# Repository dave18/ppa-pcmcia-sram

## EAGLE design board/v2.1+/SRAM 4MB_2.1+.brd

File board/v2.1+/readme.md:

This version is a small change to the 2.1 board.  Changes are:

* Allows use of 8mb version of SRAM - Note, this doesn't increases the memory from 4mb as the additional address pin is grounded. It is just for compatibility.
* Board parameters brought in line with PCBWay prototyping parameters to enable cheaper production
* PCMCIA connector moved 0.5mm closer to edge of board to fit with version I found at AliExpress.  https://www.aliexpress.com/item/4000671140408.html?spm=a2g0o.order_list.order_list_main.9.21ef1802yaBDrj

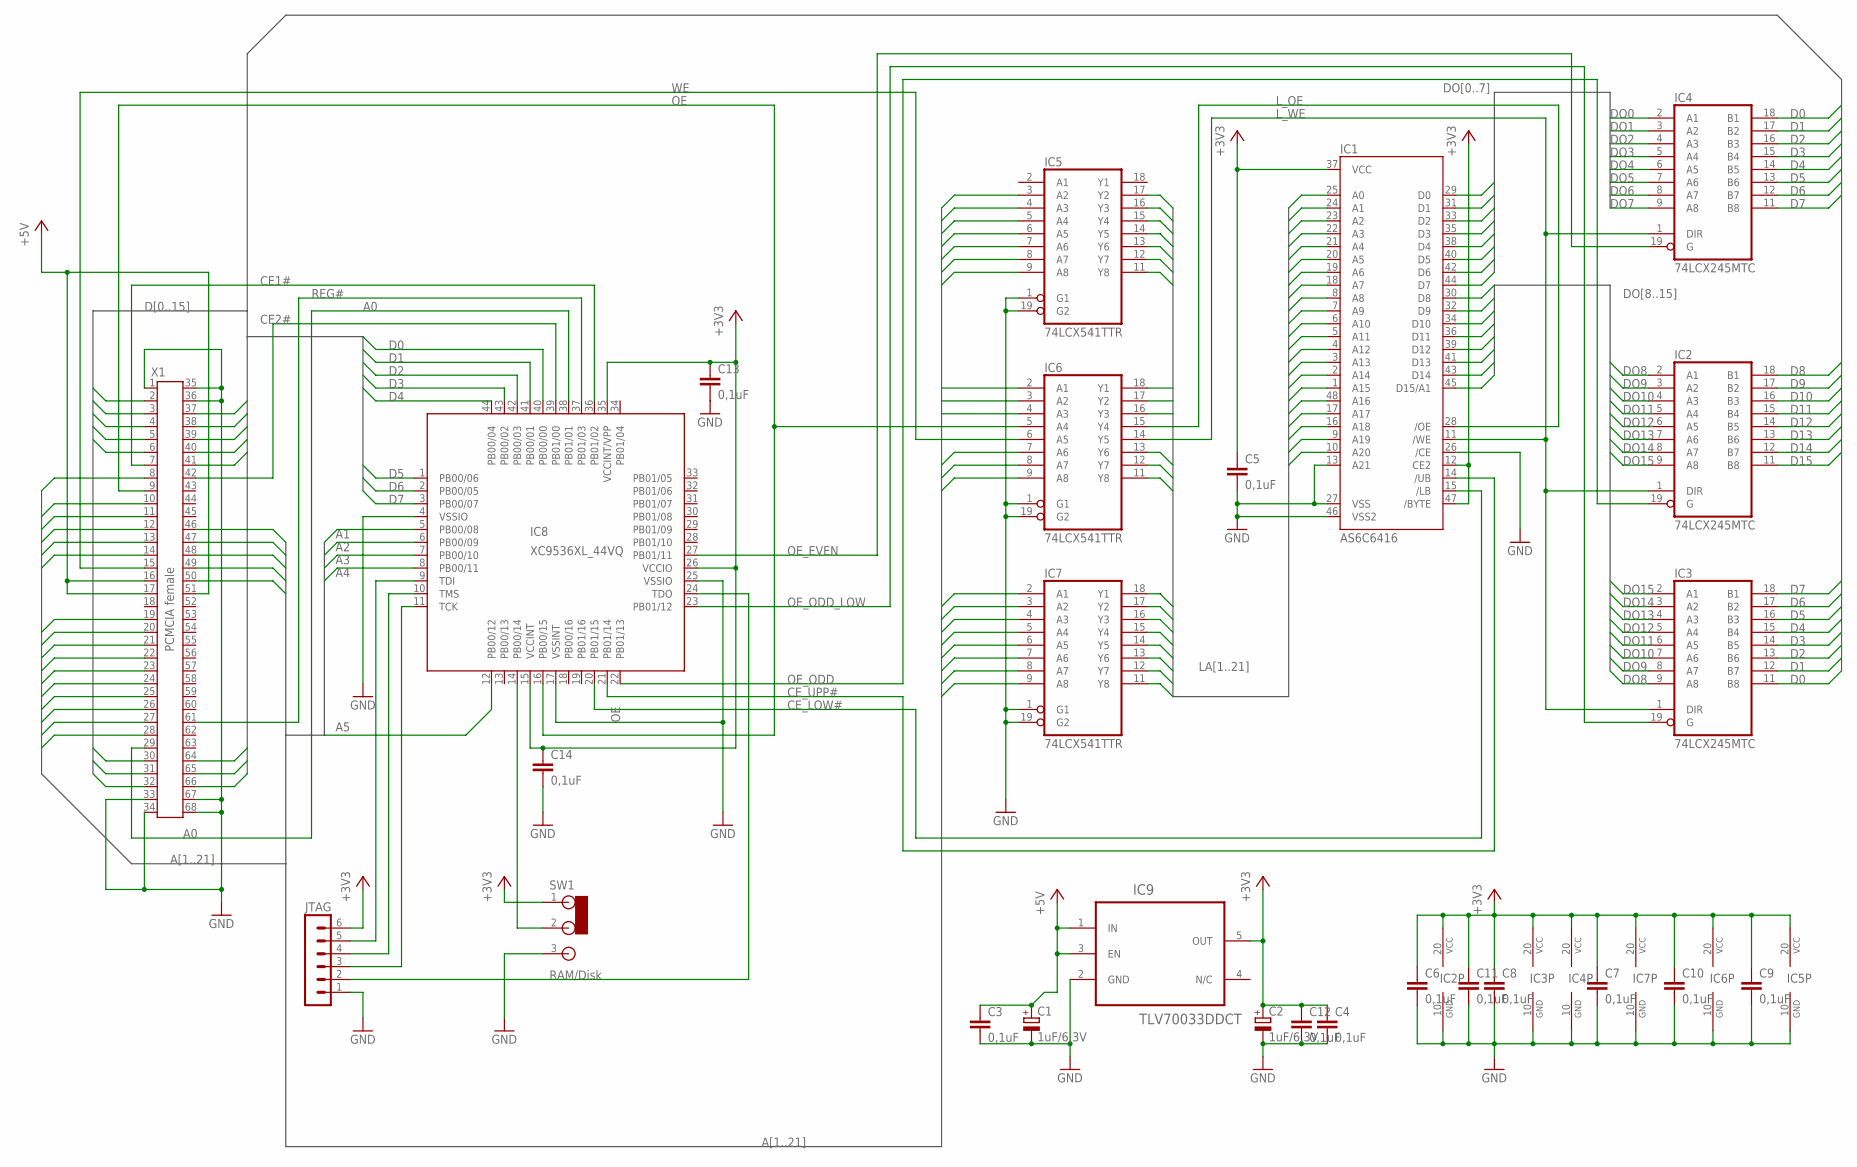
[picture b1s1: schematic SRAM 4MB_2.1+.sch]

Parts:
C1, C2: 1uF/6,3V; A/3216-18R
C3, C4: 0,1uF; C0603
C5, C6, C7, C8, C9, C10, C11, C12, C13, C14: 0,1uF; C0402K
IC1: AS6C6416; TSOP48
IC2, IC3, IC4: 74LCX245MTC; TSSOP20
IC5, IC6, IC7: 74LCX541TTR; TSSOP20
IC8: XC9536XL_44VQ; SQFP-S-10X10-44
IC9: TLV70033DDCT; SOT95P280X110-5N
JTAG: MA06-1
SW1: RAM/Disk; SWITCH2
X1: PCMCIA female; 9M681X04

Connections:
+3V3: C2.+, C4.1, C5.1, C6.1, C7.1, C8.1, C9.1, C10.1, C11.1, C12.1, C13.1, C14.1, IC1.12 (CE2), IC1.37 (VCC), IC1.47 (/BYTE), IC2.20 (VCC), IC3.20 (VCC), IC4.20 (VCC), IC5.20 (VCC), IC6.20 (VCC), IC7.20 (VCC), IC8.15 (VCCINT), IC8.26 (VCCIO), IC8.35 (VCCINT/VPP), IC9.5 (OUT), JTAG.6, SW1.1
+5V: C1.+, C3.1, IC9.1 (IN), IC9.3 (EN), X1.16, X1.17, X1.51
A0: IC8.38 (PB01/01), X1.29
A1: IC5.3 (A2), IC8.5 (PB00/08), X1.28
A2: IC5.4 (A3), IC8.6 (PB00/09), X1.27
A3: IC5.5 (A4), IC8.7 (PB00/10), X1.26
A4: IC5.6 (A5), IC8.8 (PB00/11), X1.25
A5: IC5.7 (A6), IC8.12 (PB00/12), X1.24
A6: IC5.8 (A7), X1.23
A7: IC5.9 (A8), X1.22
A8: IC7.6 (A5), X1.12
A9: IC7.7 (A6), X1.11
A10: IC7.9 (A8), X1.8
A11: IC7.8 (A7), X1.10
A12: IC6.2 (A1), X1.21
A13: IC7.4 (A3), X1.13
A14: IC7.2 (A1), X1.14
A15: IC6.3 (A2), X1.20
A16: IC6.4 (A3), X1.19
A17: IC7.5 (A4), X1.46
A18: IC7.3 (A2), X1.47
A19: IC6.9 (A8), X1.48
A20: IC6.8 (A7), X1.49
A21: IC6.7 (A6), X1.50
CE1#: IC8.36 (PB01/02), X1.7
CE2#: IC8.39 (PB01/00), X1.42
CE_LOW#: IC1.15 (/LB), IC8.20 (PB01/15)
CE_UPP#: IC1.14 (/UB), IC8.21 (PB01/14)
D0: IC3.11 (B8), IC4.18 (B1), IC8.40 (PB00/00), X1.30
D1: IC3.12 (B7), IC4.17 (B2), IC8.41 (PB00/01), X1.31
D2: IC3.13 (B6), IC4.16 (B3), IC8.42 (PB00/03), X1.32
D3: IC3.14 (B5), IC4.15 (B4), IC8.43 (PB00/02), X1.2
D4: IC3.15 (B4), IC4.14 (B5), IC8.44 (PB00/04), X1.3
D5: IC3.16 (B3), IC4.13 (B6), IC8.1 (PB00/06), X1.4
D6: IC3.17 (B2), IC4.12 (B7), IC8.2 (PB00/05), X1.5
D7: IC3.18 (B1), IC4.11 (B8), IC8.3 (PB00/07), X1.6
D8: IC2.18 (B1), X1.64
D9: IC2.17 (B2), X1.65
D10: IC2.16 (B3), X1.66
D11: IC2.15 (B4), X1.37
D12: IC2.14 (B5), X1.38
D13: IC2.13 (B6), X1.39
D14: IC2.12 (B7), X1.40
D15: IC2.11 (B8), X1.41
DO0: IC1.29 (D0), IC4.2 (A1)
DO1: IC1.31 (D1), IC4.3 (A2)
DO2: IC1.33 (D2), IC4.4 (A3)
DO3: IC1.35 (D3), IC4.5 (A4)
DO4: IC1.38 (D4), IC4.6 (A5)
DO5: IC1.40 (D5), IC4.7 (A6)
DO6: IC1.42 (D6), IC4.8 (A7)
DO7: IC1.44 (D7), IC4.9 (A8)
DO8: IC1.30 (D8), IC2.2 (A1), IC3.9 (A8)
DO9: IC1.32 (D9), IC2.3 (A2), IC3.8 (A7)
DO10: IC1.34 (D10), IC2.4 (A3), IC3.7 (A6)
DO11: IC1.36 (D11), IC2.5 (A4), IC3.6 (A5)
DO12: IC1.39 (D12), IC2.6 (A5), IC3.5 (A4)
DO13: IC1.41 (D13), IC2.7 (A6), IC3.4 (A3)
DO14: IC1.43 (D14), IC2.8 (A7), IC3.3 (A2)
DO15: IC1.45 (D15/A1), IC2.9 (A8), IC3.2 (A1)
GND: C1.-, C2.-, C3.2, C4.2, C5.2, C6.2, C7.2, C8.2, C9.2, C10.2, C11.2, C12.2, C13.2, C14.2, IC1.13 (A21), IC1.26 (/CE), IC1.27 (VSS), IC1.46 (VSS2), IC2.10 (GND), IC3.10 (GND), IC4.10 (GND), IC5.1 (G1), IC5.10 (GND), IC5.19 (G2), IC6.1 (G1), IC6.10 (GND), IC6.19 (G2), IC7.1 (G1), IC7.10 (GND), IC7.19 (G2), IC8.4 (VSSIO), IC8.17 (VSSINT), IC8.25 (VSSIO), IC9.2 (GND), JTAG.1, SW1.3, X1.1, X1.33, X1.34, X1.35, X1.36, X1.67, X1.68
LA1: IC1.25 (A0), IC6.16 (Y3)
LA2: IC1.24 (A1), IC5.17 (Y2)
LA3: IC1.23 (A2), IC5.16 (Y3)
LA4: IC1.22 (A3), IC5.15 (Y4)
LA5: IC1.21 (A4), IC5.14 (Y5)
LA6: IC1.20 (A5), IC5.13 (Y6)
LA7: IC1.19 (A6), IC5.12 (Y7)
LA8: IC1.18 (A7), IC5.11 (Y8)
LA9: IC1.8 (A8), IC6.11 (Y8)
LA10: IC1.7 (A9), IC7.11 (Y8)
LA11: IC1.6 (A10), IC7.12 (Y7)
LA12: IC1.5 (A11), IC7.13 (Y6)
LA13: IC1.4 (A12), IC7.14 (Y5)
LA14: IC1.3 (A13), IC7.15 (Y4)
LA15: IC1.2 (A14), IC7.16 (Y3)
LA16: IC1.1 (A15), IC7.17 (Y2)
LA17: IC1.48 (A16), IC7.18 (Y1)
LA18: IC1.17 (A17), IC6.18 (Y1)
LA19: IC1.16 (A18), IC6.17 (Y2)
LA20: IC1.9 (A19), IC6.12 (Y7)
LA21: IC1.10 (A20), IC6.13 (Y6)
L_OE: IC1.28 (/OE), IC6.15 (Y4)
L_WE: IC1.11 (/WE), IC2.1 (DIR), IC3.1 (DIR), IC4.1 (DIR), IC6.14 (Y5)
unnamed: IC8.24 (TDO), JTAG.2
unnamed: IC8.11 (TCK), JTAG.3
unnamed: IC8.10 (TMS), JTAG.4
unnamed: IC8.9 (TDI), JTAG.5
unnamed: IC8.14 (PB00/14), SW1.2
OE: IC6.5 (A4), IC8.16 (PB00/15), X1.9
OE_EVEN: IC4.19 (G), IC8.27 (PB01/11)
OE_ODD: IC2.19 (G), IC8.22 (PB01/13)
OE_ODD_LOW: IC3.19 (G), IC8.23 (PB01/12)
REG#: IC8.37 (PB01/03), X1.61
WE: IC6.6 (A5), X1.15

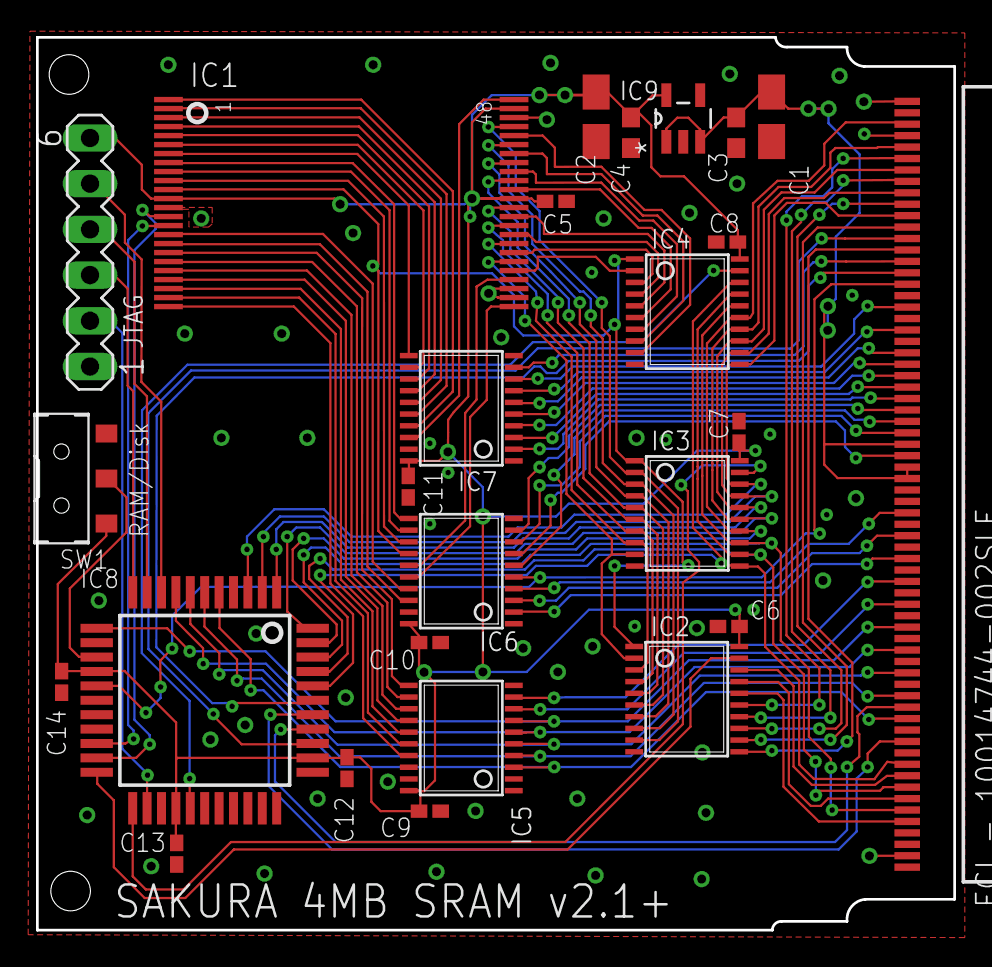
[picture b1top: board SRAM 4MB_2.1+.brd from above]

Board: 2 copper layers, 51.0 x 49.6 mm, 26 parts (0 on the bottom side), 95 nets.

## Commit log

2023-03-23 Create v2.1+
